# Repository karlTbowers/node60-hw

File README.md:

# Node60 — Automotive 10BASE-T1S Power Distribution Node

Open-hardware six-output automotive power distribution node by DropOut. Each output is a protected smart high-side switch with current and voltage telemetry, reported over a multidrop 10BASE-T1S network.

**Status:** Architecture Rev A, schematic capture starting. Not yet validated hardware.

**Architecture and design documentation:** https://karltbowers.github.io/node60-hw/ (source in [`docs/`](docs/)).

| | |
|---|---|
| MCU | NXP S32K344 |
| Network | Microchip LAN8670 10BASE-T1S PHY (RMII), PLCA follower |
| Outputs | 6 × 10 A target, 3 × TI TPS2HCS08A-Q1 dual smart eFuses |
| Input | 12 V battery-direct, TI LM74910H-Q1 ideal diode + 75 A breaker |
| Tools | KiCad 10, Zephyr RTOS (firmware in a separate repo) |

## Cloning

The DropOut part library is a git submodule, so clone recursively:

```bash
git clone --recursive https://github.com/karlTbowers/node60-hw.git
```

Already cloned without it? Run `git submodule update --init`.

## Workstation

To set up a new Apple-silicon Mac with the whole design environment, run `scripts/setup-workstation.sh`. It installs KiCad 10.0.7, the Homebrew tools, the DropOut repos, KiCadRoutingTools and its Python, then checks that the Mac reproduces the reference judging run. See [`scripts/workstation/README.md`](scripts/workstation/README.md).

## Layout

```
node60.kicad_pro / .kicad_sch / .kicad_pcb    KiCad 10 project; node60.kicad_sch is the root sheet (page 1, index)
sheets/                                       every other schematic sheet, flat (handbook ch. 05)
scripts/check_schematic.py                    CI check: sheet files, page numbers, reference designators
sym-lib-table, fp-lib-table                   point into lib/ — do not use global DropOut tables
lib/dropout-kicad-library/                    submodule: symbols, footprints, 3D models
docs/                                         Starlight documentation site: architecture, calculations, test plans
.github/workflows/ci.yml                      ERC/DRC on every push; fab outputs on tags
.github/workflows/docs.yml                    builds docs/ on PRs; deploys main to GitHub Pages
```

## Library

All parts come from [dropout-kicad-library](https://github.com/karlTbowers/dropout-kicad-library). The project library tables use `${KIPRJMOD}/lib/dropout-kicad-library/...`, so nothing needs to be configured in KiCad's global settings.

Update the library:

```bash
git -C lib/dropout-kicad-library pull origin main
git add lib/dropout-kicad-library
git commit -m "Update DropOut library"
```

## Releases

Board revisions are git tags: `rev-a`, `rev-b`, … Pushing a tag makes CI run ERC and DRC and attach the fabrication package (Gerbers, drill, position file, BOM, schematic PDF) to a GitHub Release.

```bash
git tag rev-a && git push origin rev-a
```

## License

TBD — to be chosen before the first public release.

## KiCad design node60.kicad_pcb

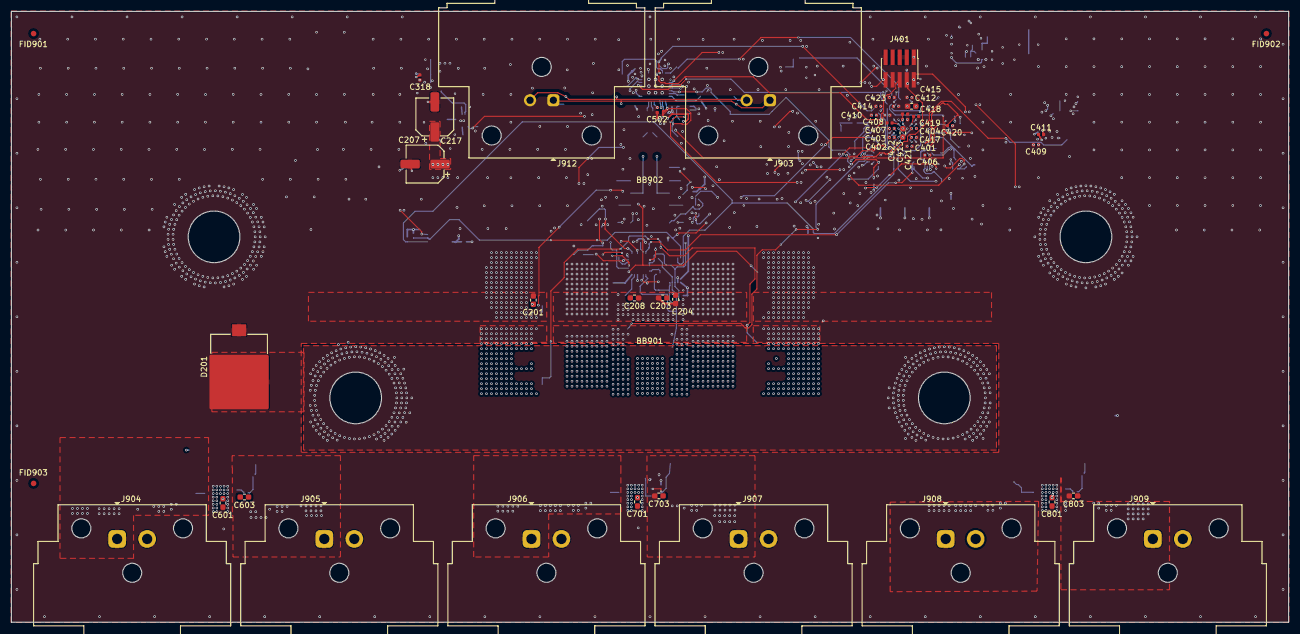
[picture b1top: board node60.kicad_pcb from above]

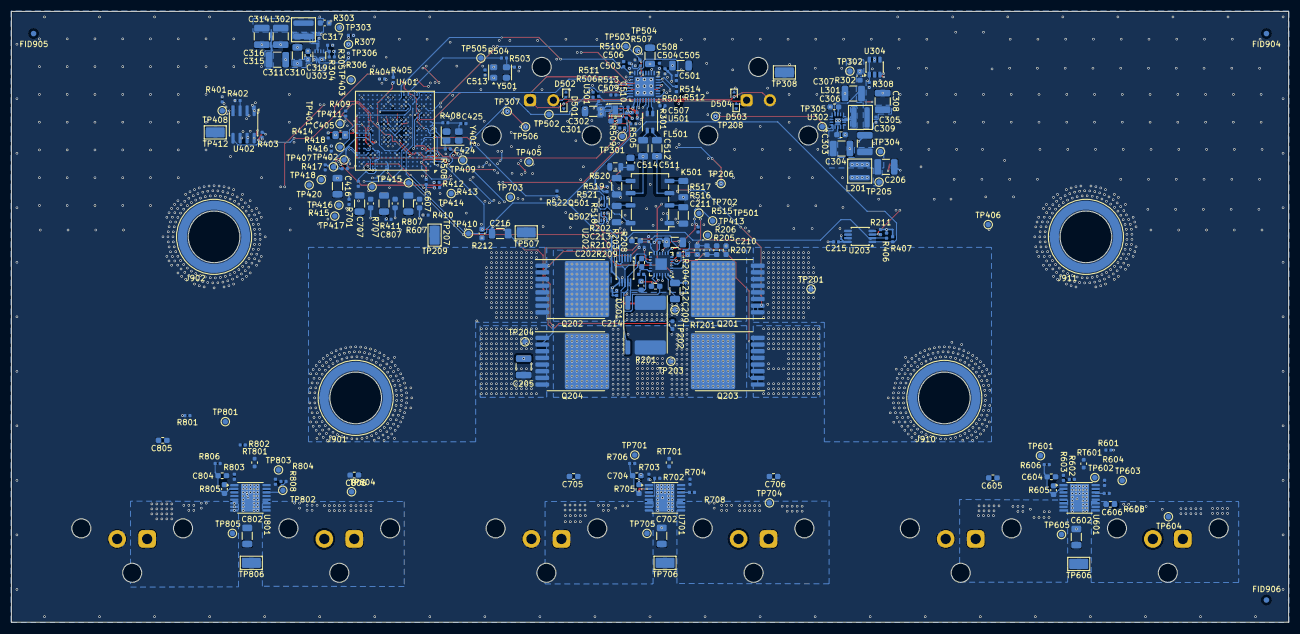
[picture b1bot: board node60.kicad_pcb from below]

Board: 6 copper layers, 230.0 x 110.0 mm, 293 parts (243 on the bottom side), 136 nets.

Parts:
BB901: Busbar_Cu_19.05x3.175mm_L125.05mm_2xD6.5mm_P106mm
BB902: Busbar_Cu_19.05x3.175mm_L176.05mm_2xD6.5mm_P157mm
C201, C203, C204, C208, C303, C310, C601, C605, C606, C701, C705, C706, C801, C805, C806: 100nF; C_0603_1608Metric
C202, C210, C212, C213: 10nF; C_0603_1608Metric
C205, C206, C304, C305: 4.7uF; C_1210_3225Metric
C207, C217: 47uF; CP_Elec_6.3x7.7
C209, C301, C602, C702, C802: 1uF; C_1206_3216Metric
C211: 68nF; C_1206_3216Metric
C214, C215, C309, C317, C318, C401, C402, C403, C404, C406, C407, C408, C409, C410, C411, C412, C413, C414, C417, C418, C419, C420, C423, C502, C504, C507, C510, C513: 100nF; C_0402_1005Metric
C216, C511, C512, C607, C707, C807: 100nF; C_1206_3216Metric
C302, C421: 2.2uF; C_0603_1608Metric
C306, C415: 1uF; C_0603_1608Metric
C307, C308, C314, C315, C316: 22uF; C_1210_3225Metric
C311, C416, C505, C508: 10uF; C_1206_3216Metric
C319, C424, C425: 10pF; C_0402_1005Metric
C405: 4.7uF; C_0805_2012Metric
C422: 220nF; C_0402_1005Metric
C501, C503, C506, C509: 10nF; C_0402_1005Metric
C514: 100nF; C_0805_2012Metric
C603, C703, C803: 470nF; C_0603_1608Metric
C604, C704, C804: 4.7nF; C_0603_1608Metric
D201: XLD8A24CAHM3_A_I; D_DO-218AC
D501, D502, D503, D504: VETH100A1DD1HG3-08; Vishay_DFN1006-2B_1.0x0.6mm
FID901, FID902, FID903, FID904, FID905, FID906: Fiducial_1mm_Mask2mm
FL501: ACT1210E-241-2P-TL00; L_CommonModeChoke_TDK_ACT1210E_3.2x2.5mm
J401: FTSH-105-01-L-DV-K; Samtec_FTSH-105-01-x-DV_2x05_P1.27mm_Vertical_SMD
J901, J902, J910, J911: 74660016R; Wuerth_REDCUBE-SMT_WP-SMRT_74660016
J903, J912: ATM13-2P-BM04; Amphenol_ATM13-2P-BMxx_1x02_P4.20mm_Horizontal
J904, J905, J906, J907, J908, J909: AT13-2P-BM04; Amphenol_AT13-2P-BMxx_1x02_P5.40mm_Horizontal
K501: G6KU-2F-Y-T1-TRS_DC3; Relay_DPDT_Omron_G6K-2F-Y
L201, L301: 74438356022HT; L_Wuerth_MAPI-4020
L302: 744383560056HT; L_Wuerth_MAPI-4020
Q201, Q202, Q203, Q204: IAUTN08S5N012LATMA1; Infineon_PG-HSOF-8-2
Q501, Q502: DMC2710UVQ-7; Diodes_SOT-563
R201: BVR-Z-R0003-1.0; R_Shunt_Isabellenhuette_BVR4026
R202, R601, R701, R801: 10R; R_0402_1005Metric
R203, R211, R401, R402, R403, R404, R405, R505, R506, R507, R508, R509, R510, R511, R512, R513, R514, R515, R602, R603, R606, R702, R703, R706, R802, R803, R806: 10k; R_0402_1005Metric
R204: 107k; R_0603_1608Metric
R205: 2k; R_0603_1608Metric
R206: 7.87k; R_0603_1608Metric
R207: 2.1k; R_0603_1608Metric
R208: 26.7k; R_0402_1005Metric
R209: 49.9R; R_0603_1608Metric
R210: 383R; R_0402_1005Metric
R212, R607, R707, R807: 10k; R_0603_1608Metric
R301, R408: 0R; R_0402_1005Metric
R302, R303: 0R; R_0603_1608Metric
R304: 76.8k; R_0402_1005Metric
R305: 51k; R_0402_1005Metric
R306, R307, R521, R522: 100k; R_0402_1005Metric
R308, R604, R704, R804: 4.7k; R_0402_1005Metric
R406, R407: 2.2k; R_0402_1005Metric
R409, R410, R411, R412, R413, R414, R415, R416, R417, R418, R503, R504, R608, R708, R808: 33R; R_0402_1005Metric
R501: 12.4k; R_0402_1005Metric
R516, R518: 1.5k; R_1206_3216Metric
R517, R519: 49.9R; R_1206_3216Metric
R520: 100k; R_0805_2012Metric
R605, R705, R805: 698R; R_0603_1608Metric
RT201, RT601, RT701, RT801: NCU18XH103F6SRB; R_NTC_0603_1608Metric_Pad0.7x0.7mm
TP201, TP202, TP203, TP204, TP205, TP206, TP207, TP208, TP301, TP302, TP303, TP304, TP305, TP306, TP307, TP401, TP402, TP403, TP405, TP406, TP407, TP408, TP409, TP410, TP411, TP413, TP414, TP415, TP416, TP417, TP418, TP420, TP501, TP502, TP503, TP504, TP505, TP506, TP601, TP602, TP603, TP604, TP605, TP701, TP702, TP703, TP704, TP705, TP801, TP802, TP803, TP804, TP805: TestPoint_Pad_D1.0mm
TP209, TP308, TP412, TP507, TP606, TP706, TP806: S1751-46R; TestPoint_Harwin_S1751
U201: LM74910HQRGERQ1; Texas_RGE0024T_VQFN-24-1EP_4x4mm_P0.5mm_EP2.1x2.1mm
U202: INA228AQDGSRQ1; Texas_DGS0010A_TSSOP-10_3x3mm_P0.5mm
U203: TMP175AQDGKRQ1; Texas_DGK0008A_TSSOP-8_3x3mm_P0.65mm
U301: TPS7B8133QWDRVRQ1; Texas_DRV0006A_WSON-6-1EP_2x2mm_P0.65mm_EP1x1.6mm
U302: LMQ66430MC3RXBRQ1; Texas_RXB0014A_VQFN-14-1EP_2.6x2.6mm_P0.5mm_EP1x1mm
U303: TPS628502QDRLRQ1; Texas_DRL0008A_SOT-583-8
U304: TPS3702AX33QDDCRQ1; Texas_DDC0006A_TSOT-23-6
U401: S32K344EHT1MMMST; NXP_LFBGA-257_14x14mm_Layout17x17_P0.8mm
U402: IS25LP032D-JNLA3; SOIC-8_3.9x4.9mm_P1.27mm
U501: LAN8670D0-E_LMXVAO; Microchip_LMX_VQFN-32-1EP_5x5mm_P0.5mm_EP3.5x3.5mm
U601, U701, U801: TPS2HCS08AQPWPRQ1; HTSSOP-16-1EP_4.4x5mm_P0.65mm_EP3.4x5mm_Mask2.78x3.313mm
Y401: ABM8AIG-16.000MHZ-8-1Z-T; Crystal_SMD_NDK_NX3225SA-4Pin_3.2x2.5mm
Y501: ECS-3225SMVQ-500-DS-TR; Oscillator_SMD_ECS_LGA-4_2.5x3.2mm_P2.3mm

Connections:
1V5_CORE: C401.1, C402.1, C403.1, C404.1, C405.1, R303.2, TP303.1, U401.H8, U401.H10, U401.K8, U401.K10
3V3_MAIN: C214.1, C215.1, C310.1, C311.1, C318.1, C406.1, C407.1, C408.1, C409.1, C410.1, C411.1, C412.1, C413.1, C414.1, C415.1, C416.1, C423.1, C501.1, C502.1, C503.1, C504.1, C505.1, C506.1, C507.1, C508.1, C513.1, J401.1, Q501.4, Q502.4, R203.1, R211.1, R212.1, R302.2, R306.1, R308.1, R401.1, R402.1, R403.1, R404.1, R406.1, R407.1, R505.1, R506.1, R507.1, R508.1, R601.1, R607.1, R701.1, R707.1, R801.1, R807.1, TP302.1, U202.6, U203.8, U303.1, U303.3, U303.4, U304.3, U304.5, U401.D14, U401.G10, U401.H6, U401.H7, U401.K11, U401.L8, U401.N4, U401.R7, U401.R10, U402.8, U501.8, U501.18, U501.29, Y501.1, Y501.4
/BATT_MON: C210.1, R205.2, R206.1, TP206.1, U401.B1
/I2C0_TELEMETRY_SCL: R406.2, TP409.1, U202.5, U203.2, U401.M4
/I2C0_TELEMETRY_SDA: R407.2, TP410.1, U202.4, U203.1, U401.P5
/INH: R515.1, TP208.1, TP305.1, TP501.1, U201.7, U302.1, U501.1
/LM_FLT_L: R203.2, TP207.1, U201.12, U401.B11
/MCU and NVM/1V1_MCU_V11: C417.1, C418.1, C419.1, C420.1, C421.1, TP411.1, U401.H9, U401.J8, U401.J10, U401.K9
/MCU and NVM/2V5_MCU_V25: C422.1, U401.J7
/MCU and NVM/FLASH_HOLD_L: R403.2, U402.7
/MCU and NVM/FLASH_WP_L: R402.2, U402.3
/MCU and NVM/FXOSC_EXTAL: C424.1, U401.K1, Y401.1
/MCU and NVM/FXOSC_XTAL: R408.1, U401.L1
/MCU and NVM/FXOSC_XTAL_X: C425.1, R408.2, Y401.3
/MCU and NVM/SPI2_FLASH_CS_L: R401.2, TP408.1, U401.E1, U402.1
/MCU and NVM/SPI2_FLASH_MISO: U401.C2, U402.2
/MCU and NVM/SPI2_FLASH_MOSI: U401.C6, U402.5
/MCU and NVM/SPI2_FLASH_SCK: R418.2, TP407.1, U402.6
/MCU and NVM/SPI2_FLASH_SCK_MCU: R418.1, U401.D2
/MCU and NVM/SPI3_SWITCH3_CS_L_MCU: R417.1, U401.G15
/MCU and NVM/SPI3_SWITCH3_MOSI_MCU: R416.1, U401.F14
/MCU and NVM/SPI3_SWITCH3_SCK_MCU: R415.1, U401.E14
/MCU and NVM/SPI4_SWITCH1_CS_L_MCU: R411.1, U401.A14
/MCU and NVM/SPI4_SWITCH1_MOSI_MCU: R410.1, U401.C15
/MCU and NVM/SPI4_SWITCH1_SCK_MCU: R409.1, U401.D15
/MCU and NVM/SPI5_SWITCH2_CS_L_MCU: R414.1, U401.G16
/MCU and NVM/SPI5_SWITCH2_MOSI_MCU: R413.1, U401.A15
/MCU and NVM/SPI5_SWITCH2_SCK_MCU: R412.1, U401.A16
/MCU and NVM/SWD_CLK: J401.4, R405.1, U401.F7
/MCU and NVM/SWD_DIO: J401.2, R404.2, U401.F6
/MCU and NVM/SWD_SWO: J401.6, U401.G8
/MCU and NVM/UART0_DEBUG_RX: TP402.1, U401.D17
/MCU and NVM/UART0_DEBUG_TX: TP401.1, U401.E16
/MDIO0_T1S_MDC: TP503.1, U401.N3, U501.13
/MDIO0_T1S_MDIO: R507.2, TP504.1, U401.P2, U501.14
/NTC_RSENSE: C216.1, R212.2, RT201.1, U401.C1
/NTC_SW1: C607.1, R607.2, RT601.1, U401.E4
/NTC_SW2: C707.1, R707.2, RT701.1, U401.F9
/NTC_SW3: C807.1, R807.2, RT801.1, U401.B9
/OUT1: C606.1, J904.1, TP604.1, U601.9, U601.10, U601.11
/OUT2: C605.1, J905.1, TP605.1, U601.6, U601.7, U601.8
/OUT3: C706.1, J906.1, TP704.1, U701.9, U701.10, U701.11
/OUT4: C705.1, J907.1, TP705.1, U701.6, U701.7, U701.8
/OUT5: C806.1, J908.1, TP804.1, U801.9, U801.10, U801.11
/OUT6: C805.1, J909.1, TP805.1, U801.6, U801.7, U801.8
/Outputs 1-2/SW_DI: R602.1, U601.4
/Outputs 1-2/SW_SDO: R608.1, U601.14
/Outputs 1-2/SW_SNS: C604.1, R605.1, R606.1, U601.2
/Outputs 1-2/SW_VDD: C603.1, R601.2, R604.2, U601.3
/Outputs 3-4/SW_DI: R702.1, U701.4
/Outputs 3-4/SW_SDO: R708.1, U701.14
/Outputs 3-4/SW_SNS: C704.1, R705.1, R706.1, U701.2
/Outputs 3-4/SW_VDD: C703.1, R701.2, R704.2, U701.3
/Outputs 5-6/SW_DI: R802.1, U801.4
/Outputs 5-6/SW_SDO: R808.1, U801.14
/Outputs 5-6/SW_SNS: C804.1, R805.1, R806.1, U801.2
/Outputs 5-6/SW_VDD: C803.1, R801.2, R804.2, U801.3
/Power entry/DGATE: Q201.1, Q201.2, Q202.1, Q202.2, U201.1
/Power entry/HGATE: R202.2, U201.14
/Power entry/HGATE_G: C202.1, Q203.1, Q203.2, Q204.1, Q204.2, R202.1
/Power entry/LM_CAP: C209.2, U201.23
/Power entry/LM_CSP: C212.2, R209.2, U201.20
/Power entry/LM_ILIM: R208.1, U201.11
/Power entry/LM_ISCP: C213.1, R210.2, U201.18
/Power entry/LM_OV: R206.2, R207.1, U201.5
/Power entry/LM_SW: R204.1, U201.3
/Power entry/LM_TMR: C211.1, U201.9
/Power entry/LM_UVLO: R204.2, R205.1, U201.4
/Power entry/RS_SENSE_N: C212.1, C213.2, R201.3, U201.19, U202.9
/Power entry/RS_SENSE_P: R201.2, R209.1, R210.1, U202.10
/Power entry/VBAT_D: C208.1, C209.1, Q201.9, Q202.9, R201.1, TP202.1, U201.6, U201.22, U201.24
/Power entry/VBAT_Q2D: Q203.9, Q204.9, R201.4, TP203.1
/RESET_L: J401.10, R308.2, TP307.1, TP506.1, U304.1, U304.6, U401.A3, U501.10
/RMII0_T1S_CRS_DV: R509.1, U401.R6, U501.20
/RMII0_T1S_REF_CLK: R504.2, TP505.1, U401.U6
/RMII0_T1S_RXD0: R510.1, U401.T8, U501.16
/RMII0_T1S_RXD1: R511.1, U401.U7, U501.19
/RMII0_T1S_RX_ER: R505.2, U401.P6, U501.21
/RMII0_T1S_TXD0: U401.U4, U501.6
/RMII0_T1S_TXD1: U401.T4, U501.5
/RMII0_T1S_TX_EN: R514.1, U401.R5, U501.7
/Regulators/1V5_CORE_FB: C319.2, R304.2, R305.1, U303.5
/Regulators/1V5_CORE_REG: C314.1, C315.1, C316.1, C317.1, C319.1, L302.2, R303.1, R304.1
/Regulators/1V5_CORE_SW: L302.1, U303.7
/Regulators/1V5_EN: R306.2, R307.1, TP306.1, U303.2
/Regulators/3V3_MAIN_REG: C307.1, C308.1, C309.1, L301.2, R302.1, U302.11
/Regulators/3V3_MAIN_SW: L301.1, U302.7
/Regulators/3V3_MAIN_VCC: C306.1, U302.10
/Regulators/VDDAU_AON_REG: C302.1, R301.1, U301.6
/SPI3_SWITCH3_CS_L: R417.2, TP420.1, U801.15
/SPI3_SWITCH3_MISO: R808.2, TP803.1, U401.E15
/SPI3_SWITCH3_MOSI: R416.2, TP418.1, U801.13
/SPI3_SWITCH3_SCK: R415.2, TP417.1, U801.16
/SPI4_SWITCH1_CS_L: R411.2, TP406.1, U601.15
/SPI4_SWITCH1_MISO: R608.2, TP405.1, TP603.1, U401.C17
/SPI4_SWITCH1_MOSI: R410.2, U601.13
/SPI4_SWITCH1_SCK: R409.2, TP403.1, U601.16
/SPI5_SWITCH2_CS_L: R414.2, TP416.1, U701.15
/SPI5_SWITCH2_MISO: R708.2, TP415.1, TP703.1, U401.B13
/SPI5_SWITCH2_MOSI: R413.2, TP414.1, U701.13
/SPI5_SWITCH2_SCK: R412.2, TP413.1, U701.16
/SW1_FLT_L: R604.1, TP602.1, U401.B5, U601.12
/SW1_SNS: R606.2, TP601.1, U401.A7
/SW2_FLT_L: R704.1, TP702.1, U401.A5, U701.12
/SW2_SNS: R706.2, TP701.1, U401.A9
/SW3_FLT_L: R804.1, TP802.1, U401.B10, U801.12
/SW3_SNS: R806.2, TP801.1, U401.A10
/SW_LHI: R603.1, R703.1, R803.1, U401.G6, U601.5, U701.5, U801.5
/T1S/T1S_CMC_N: C512.1, FL501.4
/T1S/T1S_CMC_P: C511.1, FL501.3
/T1S/T1S_MODE0: R513.1, U501.23
/T1S/T1S_MODE1: R506.2, U501.24
/T1S/T1S_N_DROP: K501.2, R516.2
/T1S/T1S_N_END: K501.4, R517.2
/T1S/T1S_OSC_OUT: R503.1, R504.1, Y501.3
/T1S/T1S_PHYAD4: R512.1, U501.15
/T1S/T1S_PHY_N: FL501.1, U501.31
/T1S/T1S_PHY_P: FL501.2, U501.30
/T1S/T1S_P_DROP: K501.7, R518.2
/T1S/T1S_P_END: K501.5, R519.2
/T1S/T1S_RBIAS: R501.1, U501.26
/T1S/T1S_REFCLK: R503.2, U501.27
/T1S/T1S_TERM_COIL_R: K501.8, Q501.3, Q501.6
/T1S/T1S_TERM_COIL_S: K501.1, Q502.3, Q502.6
/T1S/T1S_TERM_CT: C514.1, R516.1, R517.1, R518.1, R519.1, R520.1
/T1S_IRQ_L: R508.2, TP502.1, U401.B3, U501.22
/T1S_N: C512.2, D502.2, D504.2, J903.2, J912.2, K501.3
/T1S_P: C511.2, D501.2, D503.2, J903.1, J912.1, K501.6
/T1S_TERM_DROP: Q502.2, Q502.5, R521.1, U401.E3
/T1S_TERM_END: Q501.2, Q501.5, R522.1, U401.F3
/TMP175_ALERT_L: R211.2, U203.3, U401.A11
/VBAT_IN: BB901.1, BB901.2, C201.1, D201.2, J901.1, J910.1, Q201.3, Q201.4, Q201.5, Q201.6, Q201.7, Q201.8, Q202.3, Q202.4, Q202.5, Q202.6, Q202.7, Q202.8, TP201.1, U201.2
GND: BB902.1, BB902.2, C201.2, C202.2, C203.2, C204.2, C205.2, C206.2, C207.2, C208.2, C210.2, C211.2, C214.2, C215.2, C216.2, C217.2, C301.2, C302.2, C303.2, C304.2, C305.2, C306.2, C307.2, C308.2, C309.2, C310.2, C311.2, C314.2, C315.2, C316.2, C317.2, C318.2, C401.2, C402.2, C403.2, C404.2, C405.2, C406.2, C407.2, C408.2, C409.2, C410.2, C411.2, C412.2, C413.2, C414.2, C415.2, C416.2, C417.2, C418.2, C419.2, C420.2, C421.2, C422.2, C423.2, C424.2, C425.2, C501.2, C502.2, C503.2, C504.2, C505.2, C506.2, C507.2, C508.2, C509.2, C510.2, C513.2, C514.2, C601.2, C602.2, C603.2, C604.2, C605.2, C606.2, C607.2, C701.2, C702.2, C703.2, C704.2, C705.2, C706.2, C707.2, C801.2, C802.2, C803.2, C804.2, C805.2, C806.2, C807.2, D201.1, D501.1, D502.1, D503.1, D504.1, J401.3, J401.5, J401.9, J902.1, J904.2, J905.2, J906.2, J907.2, J908.2, J909.2, J911.1, Q501.1, Q502.1, R207.2, R208.2, R305.2, R307.2, R405.2, R501.2, R509.2, R510.2, R511.2, R512.2, R513.2, R514.2, R515.2, R520.2, R521.2, R522.2, R602.2, R603.2, R605.2, R702.2, R703.2, R705.2, R802.2, R803.2, R805.2, RT201.2, RT601.2, RT701.2, RT801.2, TP209.1, TP308.1, TP412.1, TP507.1, TP606.1, TP706.1, TP806.1, U201.13, U202.1, U202.2, U202.7, U203.4, U203.5, U203.6, U203.7, U301.3, U301.4, U301.7, U302.6, U302.13, U302.15, U303.8, U304.2, U304.4, U401.B2, U401.B16, U401.D4, U401.D9, U401.G7, U401.G11, U401.J1, U401.J4, U401.J6, U401.J9, U401.J14, U401.L7, U401.L11, U401.P4, U401.P14, U401.T2, U401.T7, U401.T10, U401.T16, U402.4, U501.11, U501.32, U501.33, U601.1, U701.1, U801.1, Y401.2, Y401.4, Y501.2
VBAT_FILT: C206.1, C207.1, C217.1, C303.1, C304.1, C305.1, L201.2, TP205.1, TP304.1, U302.3
VBAT_PROT: C203.1, C204.1, C205.1, C301.1, C601.1, C602.1, C701.1, C702.1, C801.1, C802.1, L201.1, Q203.3, Q203.4, Q203.5, Q203.6, Q203.7, Q203.8, Q204.3, Q204.4, Q204.5, Q204.6, Q204.7, Q204.8, TP204.1, U201.15, U201.16, U202.8, U301.1, U301.2, U601.17, U701.17, U801.17
VDDAU_AON: C509.1, C510.1, R301.2, TP301.1, U501.25
